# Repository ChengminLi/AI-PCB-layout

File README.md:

# AI PCB Layout

A gift for hardware engineer. 

An AI agent skill for **designing, reviewing, and improving power-electronics PCBs**. This skill does not produce a PCB at the first try, instead it provides a way of how to collobrate with the AI agents to boost the productivity of PCB layout. I expect that the user has at least midlevel hardware experience, thus can provide engineering judgement to review the results.  

The skill teaches an AI coding agent (Cursor, Claude Code, Codex, or any agent that supports `SKILL.md` skills) to work like a careful power-electronics layout engineer: it traces commutation and gate loops from the switching states, derives clearance and copper limits from standards and design currents, and **stops for your approval after every step**, so you stay in control of every design decision.

> **Note:** The skill helps you reach a well-reasoned design and tells you which evidence is still missing. It does not certify safety or EMC compliance. Measurements and the applicable standards remain the final authority.

## What it covers

- **Electrical net table:** worst-case peak voltage, dv/dt, RMS current, and di/dt for each key node and current path, taken from simulation or calculation, and turned into layout constraints
- **Switching loops:** commutation cells, gate charge and discharge loops, Kelvin connections, and common-mode paths, derived per switching transition
- **Insulation:** clearance, creepage, and solid insulation derived from the applicable standard and its inputs, never copied from example values
- **Copper capability:** conductor and via sizing from worst-case RMS current and permitted temperature rise
- **Placement and routing:** functional block floorplans, routability checks, and a routing plan you approve before any copper is drawn
- **Verification:** DRC, insulation geometry, parasitic extraction, re-simulation, and thermal checks, each recorded with its evidence type (CAD check, estimate, simulation, or measurement)
- **Delivery:** fabrication and assembly outputs, and a BOM with verified datasheet and order links

It works with any topology, device technology (Si, IGBT, SiC, GaN), and CAD tool. KiCad 9 is covered in the most detail; concept mappings are included for Altium Designer, Allegro/OrCAD, Xpedition/PADS, and Fusion.

## How it works

The agent works in nine steps. After each step it delivers a short report and waits for you to reply **approve**, **approve with changes**, **redo**, or **stop**.

```mermaid
flowchart TD
    S1["1. Requirements and inputs"] -- gate --> S2["2. Architecture and limits"]
    S2 -- gate --> S3["3. Circuit and models<br/>(end-to-end only)"]
    S3 -- gate --> S4["4. Schematic, footprints, and 3D"]
    S4 -- gate --> S5["5. Design rules and stack-up"]
    S5 -- gate --> S6["6. Placement"]
    S6 -- gate --> S7["7. Routing<br/>(plan first, then block by block)"]
    S7 -- gate --> S8["8. Verification and optimization"]
    S8 -- gate --> S9["9. Delivery"]
```

You don't always need all nine steps. In step 1 you agree on a scope:

| Scope | What happens |
|---|---|
| **Review** an existing design | Reads your files and reports prioritized findings. No files are changed. |
| **Small revision** (label, footprint swap, local reroute) | Proposes the change for approval, then edits and rechecks only what it affects. |
| **Create or revise a layout** for an approved circuit | Footprints, rules, placement, routing, verification, and delivery. |
| **End-to-end design** | All nine steps, from requirements to fabrication files. |

For routing you choose who draws the copper: the agent routes everything, you route and the agent verifies, or a hybrid where the agent routes the critical nets and the rest is autorouted.

## Quick start

### 1. Install the skill

Copy the `power-pcb-design` folder into your agent's skills folder:

| Agent | Skills folder |
|---|---|
| Cursor (all projects) | `~/.cursor/skills/` |
| Cursor (one project) | `<your-project>/.cursor/skills/` |
| Claude Code | `~/.claude/skills/` |
| Codex | `~/.codex/skills/` |

On Windows (PowerShell), for Cursor:

```powershell
git clone https://github.com/ChengminLi/AI-PCB-layout.git
Copy-Item -Recurse AI-PCB-layout\power-pcb-design "$env:USERPROFILE\.cursor\skills\"
```

On macOS or Linux, for Cursor:

```bash
git clone https://github.com/ChengminLi/AI-PCB-layout.git
mkdir -p ~/.cursor/skills && cp -r AI-PCB-layout/power-pcb-design ~/.cursor/skills/
```

No Git? Click **Code → Download ZIP** on this page and copy the `power-pcb-design` folder manually. Restart your agent or open a new chat so it picks up the skill.

### 2. Ask your agent

Open your PCB project folder in the agent and describe what you want. For example:

- *"Review the layout of my 48 V to 12 V synchronous buck in KiCad 9. Don't change any files."*
- *"Improve the gate loop of Q1 and Q2 on my SiC half-bridge board."*
- *"Design a 2-layer 24 V to 5 V, 3 A synchronous buck end to end in KiCad 9."*

The agent will start with step 1: it inspects your files, asks only for the information that changes decisions, and proposes a scope and step plan for your approval.

## Repository layout

```
AI-PCB-layout/
├── power-pcb-design/        The skill
│   ├── SKILL.md             Workflow, review gates, and working rules
│   └── references/          Detailed guidance, read by the agent step by step
├── examples/                Real design examples made with the skill
└── CONTRIBUTING.md          How to add examples or improve the skill
```

The reference files cover the [electrical net table](power-pcb-design/references/electrical-net-table.md), [topologies](power-pcb-design/references/topologies.md), [devices](power-pcb-design/references/devices.md), [regimes and standards](power-pcb-design/references/regimes-and-standards.md), [CAD and tools](power-pcb-design/references/cad-and-tools.md), [electrical layout](power-pcb-design/references/electrical-layout.md), [insulation and copper](power-pcb-design/references/insulation-and-copper.md), [analysis and measurement](power-pcb-design/references/analysis-and-measurement.md), [implementation and delivery](power-pcb-design/references/implementation-and-delivery.md), and [behavioral evaluation](power-pcb-design/references/behavioral-evaluation.md).

## Examples

See [examples/](examples/) for complete boards with their design files, reports, and results.

**[EMC demonstration flyback](examples/emc-flyback-demo/)**: a 24 V to 12 V / 1 A isolated flyback for EMC lectures, with jumper "knobs" that switch filters, gate resistance, snubber, and heatsink potential. KiCad project, LTspice simulations, 39-page design report, and fabrication files.

## Contributing

Design examples, bug reports, and improvements to the skill are welcome. See [CONTRIBUTING.md](CONTRIBUTING.md).

## License

This work is licensed under the [Creative Commons Attribution 4.0 International License (CC BY 4.0)](https://creativecommons.org/licenses/by/4.0/). You may share and adapt it, including for commercial use, as long as you give credit, link to the license, and indicate if you made changes. See [LICENSE](LICENSE) for the full text.

Suggested credit: *"power-pcb-design skill by Chengmin Li, Xiao Yang, https://github.com/ChengminLi/AI-PCB-layout, licensed under CC BY 4.0."*

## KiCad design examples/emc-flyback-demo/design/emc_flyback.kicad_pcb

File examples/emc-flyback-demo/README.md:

# EMC demonstration flyback converter (24 V to 12 V)

A small isolated flyback converter built as a live demonstrator for the EMC lectures at TU/e. Jumpers on the board, the **"EMC knobs"**, switch the filter stages, the switching speed, a snubber, the potential of the heatsink case, the Y-capacitors, and the output earthing, so students can watch the conducted emissions change on two LISNs.

> **Status:** design complete and checked by calculation, simulation, and CAD rule checks. **Not yet prototyped**: the results below are predictions, not measurements.

## Design at a glance

| Item | Value |
|---|---|
| Topology | Isolated flyback, discontinuous conduction mode, peak-current mode control (UC3845B, TL431 and LTV-817S feedback) |
| Input / output | 24 V (20–30 V) in, 12.2 V / 1 A out |
| Switching frequency | 153.6 kHz, just above the 150 kHz start of CISPR band B |
| Devices | IRF520N MOSFET (100 V, TO-220) mounted on the case floor; Würth 750311591 transformer; 2 × SS510C rectifiers in parallel |
| Board | 2 layers, 100 × 76 mm, 1.6 mm FR-4, 1 oz copper |
| Mechanics | Bent 3 mm aluminium U-channel case (112 × 94 × 33 mm) that is also the MOSFET heatsink, with a clear acrylic cover |
| CAD tool | KiCad (version 7 file format; opens in KiCad 7, 8, and 9) |
| Designed with | Claude (AI agent) |
| Scope | End-to-end design, from requirements to fabrication files |
| Revision | E (3 October 2026) |

## The EMC knobs

| Jumper | Setting | Demonstrates |
|---|---|---|
| RG | 4.7 Ω / 22 Ω / 100 Ω gate resistor | Switching speed (5.0 / 2.5 / 0.65 V/ns) versus spectrum |
| CASE | Floating / PGND / chassis / 1 nF | The case is the heatsink: where its common-mode current flows |
| CM1 + CM2 | Common-mode choke bypassed | Effect of the common-mode filter |
| YCAP | Input Y-capacitors to chassis | Y-capacitor return path |
| DM | Differential-mode inductor bypassed | Effect of the differential-mode filter |
| SNUB | 100 pF + 47 Ω drain snubber | Damping of the turn-off ringing |
| YPS | 1 nF / 10 nF primary-to-secondary | External Y-capacitor across the isolation barrier |
| SGCH | Secondary ground to chassis | Earthed output: primary-secondary current through the chassis |

## Images

| | |
|---|---|
|  |  |
| The board in its case. The MOSFET sits under the board with its tab on the case floor. | Top copper. The 3 mm copper-free band in the middle separates primary and secondary. |
|  |  |
| Circuit topology with the jumper knobs in red. | Power-cell loops before (rev D) and after (rev E) the high-frequency re-layout. |

More: [bottom copper](images/pcb-bottom.png), [predicted board temperature](images/thermal-map.png).

## Results and evidence

| Criterion | Result | Evidence type |
|---|---|---|
| Output voltage and ripple | 12.22 V at 1 A, 75 mV peak-to-peak (requirement ≤ 100 mV) | Simulation (ngspice) |
| Loop stability | Phase margin 63–80° over optocoupler CTR 0.5 to 2 | Small-signal model |
| Efficiency | 83.5 % power stage; about 78–79 % for the whole board | Simulation plus loss estimate |
| MOSFET drain peak | 66 V at 24 V in, about 73 V at 30 V in (100 V rating) | Simulation and calculation |
| Loop inductance, rev D → E | Clamp loop 26 → 14 nH, snubber loop 32 → 13 nH, primary power loop 25 → 18 nH | Centre-line estimate (upper bound, for comparison) |
| Clearance and creepage | 0 of 1459 net pairs below IPC-2221B or the design rules; 2.5 mm primary-secondary | Script on the KiCad geometry, plus KiCad DRC |
| DRC and connectivity | 0 clearance errors, 0 unconnected items; schematic and PCB netlists match | CAD check |
| Temperatures at 25 °C | Clamp resistors 70 °C, MOSFET junction 41 °C (58 °C at Rg = 100 Ω) | Board thermal model |
| Conducted emissions | Not yet measured | — |

## Design findings

- **The snubber beats the gate resistor at high frequency.** In simulation, the 100 Ω gate resistor mainly lowers the 5–15 MHz band, while the RC snubber removes the 20–30 MHz ringing peak by about 20 dB. To be confirmed with LISN measurements.
- **The case is the strongest knob.** The MOSFET tab couples about 30 pF into the case. With the case on chassis and no filter, this path alone is estimated at 20–40 dB above the CISPR 32 class B limit; connecting the case to PGND returns the current locally.
- **The RCD clamp is the largest single loss** (0.91 W), more than the MOSFET at the default gate resistor.
- **Rev E shrank the high-frequency loops** by moving the clamp and snubber into the power cell, so they act within about 14 nH of the drain instead of 26–32 nH.
- **Voltage-based design rules in KiCad.** Clearances are set per net class from each net's worst-case voltage (0.6 / 0.4 / 0.2 mm, 2.5 mm across the barrier) in the project's `.kicad_dru` file, so KiCad's DRC and zone filler enforce them.

## Simulation

Two LTspice schematics in [`simulation/`](simulation/), built from the board's component values:

| File | What it simulates |
|---|---|
| `EMC_flyback_power_stage.asc` | Open-loop power stage at a fixed duty cycle: stresses, waveforms, and switching speed versus gate resistor |
| `EMC_flyback_closed_loop.asc` | Power stage plus the real control loop, with behavioural UC3845B, TL431, and LTV-817S models: regulation, load steps, cold start, efficiency |

Keep the files in one folder (clone the repository or use **Code → Download ZIP**): the closed-loop schematic needs `EMC_flyback_control.lib` and the three `.asy` symbols next to it. Each schematic has `.param` knobs (`Rg`, `SNUB`, `CTR`, `Vin`, and others) that match the jumpers on the board. The [simulation README](simulation/README.md) explains how to run them, the suggested experiments, and the reference results.

The schematics were verified in ngspice because LTspice was not available when they were made; if LTspice reports a convergence problem, see the tips at the end of the simulation README. The device models are approximate (behavioural controller models, generic diodes, a fitted MOSFET model), and common-mode paths are not modelled, so use the results for trends and margins.

## Report

The [design report](report/EMC_flyback_design_report.pdf) (39 pages) covers the calculations, simulations, thermal model, layout, mechanics, and the conducted-emission test procedure.

## Files

| Path | Content |
|---|---|
| [`report/`](report/) | Design report (PDF) |
| [`design/`](design/) | KiCad project: open `emc_flyback.kicad_pro`. Includes the custom symbol and footprint libraries, 3D models, and a [schematic PDF](design/emc_flyback_schematic.pdf) |
| [`simulation/`](simulation/) | LTspice schematics (open loop and closed loop), behavioural model library and symbols, plots, and a how-to README |
| [`outputs/`](outputs/) | Gerbers for JLCPCB, JLC BOM and placement files, full BOM with datasheet links, and hand-fitted parts list |
| [`outputs/case/`](outputs/case/) | Workshop drawing of the case and cover (PDF) and their STEP models |
| [`images/`](images/) | 3D renders, copper views, topology, loop and thermal figures |

### Notes

- **Three 3D models are not included** because of manufacturer licensing: the transformer T1 (Würth 750311591), the common-mode choke L1 (Würth 744822222), and the inductor L2 (Bourns SRN8040TA, used for its footprint-compatible body). See [design/EMC_Demo.3dshapes/README.md](design/EMC_Demo.3dshapes/README.md) to add them; without them those parts are simply missing from the 3D view.
- **Case revision.** The case STEP files keep their rev D names. Rev E moved the MOSFET, so check the position of its mounting hole (hole C, 22.74 / 49.68 mm) against the drawing before making a case.
- **Before ordering:** the LCSC number of R9/R10/R20 (UNI-ROYAL 25121WJ0472T4E) is blank in `JLC_BOM.csv`, and L2 (LCSC C37429) may be out of stock; see section 9 of the report.

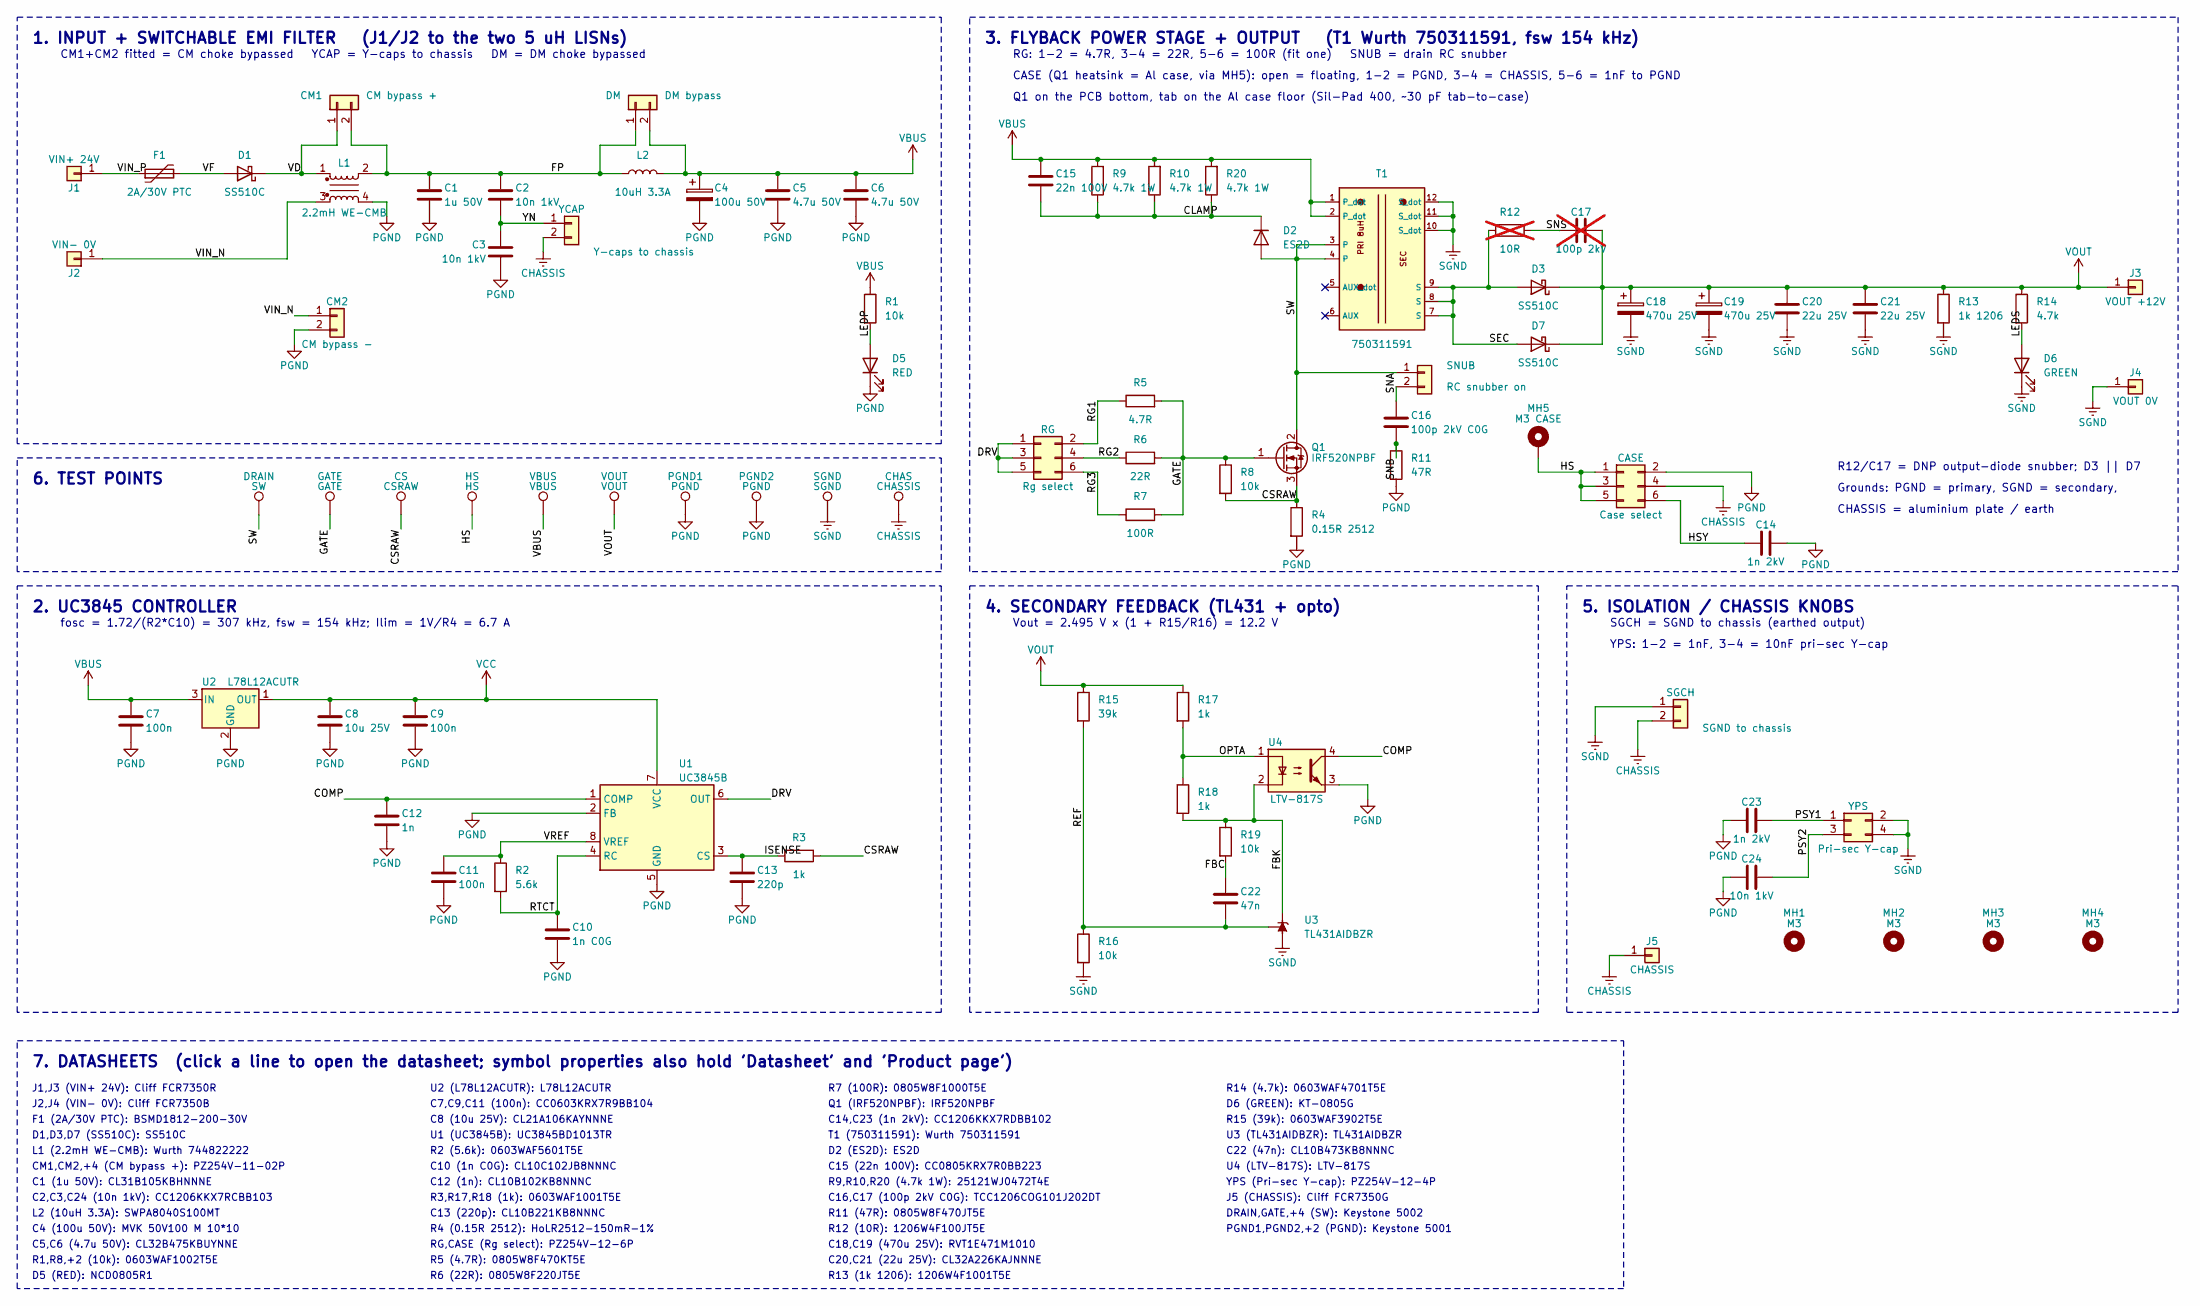
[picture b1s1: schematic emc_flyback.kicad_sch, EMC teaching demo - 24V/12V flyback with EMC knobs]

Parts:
C1: 1u 50V; C_1206_3216Metric; MPN CL31B105KBHNNNE; LCSC C1848
C2, C3, C24: 10n 1kV; C_1206_3216Metric; MPN CC1206KKX7RCBB103; LCSC C107192
C4: 100u 50V; CP_Elec_10x10; MPN MVK 50V100 M 10*10; LCSC C165627
C5, C6: 4.7u 50V; C_1210_3225Metric; MPN CL32B475KBUYNNE; LCSC C170099
C7, C9, C11: 100n; C_0603_1608Metric; MPN CC0603KRX7R9BB104; LCSC C14663
C8: 10u 25V; C_0805_2012Metric; MPN CL21A106KAYNNNE; LCSC C15850
C10: 1n C0G; C_0603_1608Metric; MPN CL10C102JB8NNNC; LCSC C163508
C12: 1n; C_0603_1608Metric; MPN CL10B102KB8NNNC; LCSC C1588
C13: 220p; C_0603_1608Metric; MPN CL10B221KB8NNNC; LCSC C1603
C14, C23: 1n 2kV; C_1206_3216Metric; MPN CC1206KKX7RDBB102; LCSC C23631
C15: 22n 100V; C_0805_2012Metric; MPN CC0805KRX7R0BB223; LCSC C107137
C16: 100p 2kV C0G; C_1206_3216Metric; MPN TCC1206COG101J202DT; LCSC C2833637
C17: 100p 2kV; C_1206_3216Metric; MPN TCC1206COG101J202DT; LCSC C2833637; not fitted
C18, C19: 470u 25V; CP_Elec_10x10; MPN RVT1E471M1010; LCSC C72518
C20, C21: 22u 25V; C_1210_3225Metric; MPN CL32A226KAJNNNE; LCSC C52306
C22: 47n; C_0603_1608Metric; MPN CL10B473KB8NNNC; LCSC C1622
CASE: Case select; PinHeader_2x03_P2.54mm_Vertical; MPN PZ254V-12-6P; LCSC C492420
CHAS: CHASSIS; TestPoint_Keystone_5000-5004_Miniature; MPN Keystone 5001 (black); LCSC C238122
CM1: CM bypass +; PinHeader_1x02_P2.54mm_Vertical; MPN PZ254V-11-02P; LCSC C492401
CM2: CM bypass -; PinHeader_1x02_P2.54mm_Vertical; MPN PZ254V-11-02P; LCSC C492401
CS: CSRAW; TestPoint_Keystone_5000-5004_Miniature; MPN Keystone 5002 (white); LCSC C238123
D1: SS510C; D_SMC; MPN SS510C (reverse-polarity); LCSC C19229
D2: ES2D; D_SMA; MPN ES2D; LCSC C364267
D3, D7: SS510C; D_SMC; MPN SS510C; LCSC C19229
D5: RED; LED_0805_2012Metric; MPN NCD0805R1; LCSC C84256
D6: GREEN; LED_0805_2012Metric; MPN KT-0805G; LCSC C2297
DM: DM bypass; PinHeader_1x02_P2.54mm_Vertical; MPN PZ254V-11-02P; LCSC C492401
DRAIN: SW; TestPoint_Keystone_5000-5004_Miniature; MPN Keystone 5002 (white); LCSC C238123
F1: 2A/30V PTC; Fuse_1812_4532Metric; MPN BSMD1812-200-30V; LCSC C960026
GATE: GATE; TestPoint_Keystone_5000-5004_Miniature; MPN Keystone 5002 (white); LCSC C238123
HS: HS; TestPoint_Keystone_5000-5004_Miniature; MPN Keystone 5002 (white); LCSC C238123
J1: VIN+ 24V; Jack_4mm_RA_Cliff_FCR7350; MPN Cliff FCR7350R (red), 4 mm right-angle 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
J2: VIN- 0V; Jack_4mm_RA_Cliff_FCR7350; MPN Cliff FCR7350B (black), 4 mm right-angl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
J3: VOUT +12V; Jack_4mm_RA_Cliff_FCR7350; MPN Cliff FCR7350R (red), 4 mm right-angle 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
J4: VOUT 0V; Jack_4mm_RA_Cliff_FCR7350; MPN Cliff FCR7350B (black), 4 mm right-angl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
J5: CHASSIS; Jack_4mm_RA_Cliff_FCR7350; MPN Cliff FCR7350G (green), 4 mm right-angl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
L1: 2.2mH WE-CMB; L_CommonMode_Wuerth_WE-CMB-S_744822222; MPN Wurth 744822222 (2.2 mH, 2 A)
L2: 10uH 3.3A; L_Bourns-SRN8040_8x8.15mm; MPN SWPA8040S100MT; LCSC C37429
MH1, MH2, MH3, MH4: M3; MountingHole_3.2mm_M3
MH5: M3 CASE; MountingHole_3.2mm_M3_Pad_Via; MPN M3 x 8 mm metal hex stand-off (female-f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
PGND1, PGND2: PGND; TestPoint_Keystone_5000-5004_Miniature; MPN Keystone 5001 (black); LCSC C238122
Q1: IRF520NPBF; TO-220-3_BottomMount_CaseHeatsink; MPN IRF520NPBF (Infineon); LCSC C2598
R1, R8, R16, R19: 10k; R_0603_1608Metric; MPN 0603WAF1002T5E; LCSC C25804
R2: 5.6k; R_0603_1608Metric; MPN 0603WAF5601T5E; LCSC C23189
R3, R17, R18: 1k; R_0603_1608Metric; MPN 0603WAF1001T5E; LCSC C21190
R4: 0.15R 2512; R_2512_6332Metric; MPN HoLR2512-150mR-1%; LCSC C500726
R5: 4.7R; R_0805_2012Metric; MPN 0805W8F470KT5E; LCSC C17675
R6: 22R; R_0805_2012Metric; MPN 0805W8F220JT5E; LCSC C17561
R7: 100R; R_0805_2012Metric; MPN 0805W8F1000T5E; LCSC C17408
R9, R10, R20: 4.7k 1W; R_2512_6332Metric; MPN 25121WJ0472T4E (UNI-ROYAL)
R11: 47R; R_0805_2012Metric; MPN 0805W8F470JT5E; LCSC C17714
R12: 10R; R_1206_3216Metric; MPN 1206W4F100JT5E; LCSC C17903; not fitted
R13: 1k 1206; R_1206_3216Metric; MPN 1206W4F1001T5E; LCSC C4410
R14: 4.7k; R_0603_1608Metric; MPN 0603WAF4701T5E; LCSC C23162
R15: 39k; R_0603_1608Metric; MPN 0603WAF3902T5E; LCSC C23153
RG: Rg select; PinHeader_2x03_P2.54mm_Vertical; MPN PZ254V-12-6P; LCSC C492420
SGCH: SGND to chassis; PinHeader_1x02_P2.54mm_Vertical; MPN PZ254V-11-02P; LCSC C492401
SGND: SGND; TestPoint_Keystone_5000-5004_Miniature; MPN Keystone 5001 (black); LCSC C238122
SNUB: RC snubber on; PinHeader_1x02_P2.54mm_Vertical; MPN PZ254V-11-02P; LCSC C492401
T1: 750311591; Wurth_750311591_EFD25; MPN Wurth 750311591 (8 uH, 1.5:1:0.67, EFD2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
U1: UC3845B; SOIC-8_3.9x4.9mm_P1.27mm; MPN UC3845BD1013TR; LCSC C7118
U2: L78L12ACUTR; SOT-89-3; MPN L78L12ACUTR; LCSC C69601
U3: TL431AIDBZR; SOT-23; MPN TL431AIDBZR; LCSC C23892
U4: LTV-817S; SMDIP-4_W9.53mm; MPN LTV-817S; LCSC C189217
VBUS: VBUS; TestPoint_Keystone_5000-5004_Miniature; MPN Keystone 5002 (white); LCSC C238123
VOUT: VOUT; TestPoint_Keystone_5000-5004_Miniature; MPN Keystone 5002 (white); LCSC C238123
YCAP: Y-caps to chassis; PinHeader_1x02_P2.54mm_Vertical; MPN PZ254V-11-02P; LCSC C492401
YPS: Pri-sec Y-cap; PinHeader_2x02_P2.54mm_Vertical; MPN PZ254V-12-4P; LCSC C492419

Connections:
AUX_A: T1.5 (AUX_dot)
AUX_B: T1.6 (AUX)
CHASSIS: CASE.4, CHAS.1, J5.1, SGCH.2, YCAP.2
CLAMP: C15.1, D2.1 (K), R9.1, R10.1, R20.1
COMP: C12.1, U1.1 (COMP), U4.4
CSRAW: CS.1, Q1.3 (S), R3.1, R4.1, R8.2
DRV: RG.1, RG.3, RG.5, U1.6 (OUT)
FBC: C22.1, R19.2
FBK: R18.2, R19.1, U3.1 (K), U4.2
FP: C1.1, C2.1, CM1.2, DM.1, L1.2, L2.1
GATE: GATE.1, Q1.1 (G), R5.2, R6.2, R7.2, R8.1
HS: CASE.1, CASE.3, CASE.5, HS.1, MH5.1
HSY: C14.1, CASE.6
ISENSE: C13.1, R3.2, U1.3 (CS)
LEDP: D5.2 (A), R1.2
LEDS: D6.2 (A), R14.2
OPTA: R17.2, R18.1, U4.1
PGND: C1.2, C3.2, C4.2, C5.2, C6.2, C7.2, C8.2, C9.2, C10.2, C11.2, C12.2, C13.2, C14.2, C23.1, C24.1, CASE.2, CM2.2, D5.1 (K), L1.4, PGND1.1, PGND2.1, R4.2, R11.2, U1.2 (FB), U1.5 (GND), U2.2 (GND), U4.3
PSY1: C23.2, YPS.1
PSY2: C24.2, YPS.3
REF: C22.2, R15.2, R16.1, U3.2 (REF)
RG1: R5.1, RG.2
RG2: R6.1, RG.4
RG3: R7.1, RG.6
RTCT: C10.1, R2.2, U1.4 (RC)
SEC: D3.2 (A), D7.2 (A), R12.1, T1.7 (S), T1.8 (S), T1.9 (S)
SGND: C18.2, C19.2, C20.2, C21.2, D6.1 (K), J4.1, R13.2, R16.2, SGCH.1, SGND.1, T1.10 (S_dot), T1.11 (S_dot), T1.12 (S_dot), U3.3 (A), YPS.2, YPS.4
SNA: C16.1, SNUB.2
SNB: C16.2, R11.1
SNS: C17.1, R12.2
SW: D2.2 (A), DRAIN.1, Q1.2 (D), SNUB.1, T1.3, T1.4
VBUS: C4.1, C5.1, C6.1, C7.1, C15.2, DM.2, L2.2, R1.1, R9.2, R10.2, R20.2, T1.1 (P_dot), T1.2 (P_dot), U2.3 (IN), VBUS.1
VCC: C8.1, C9.1, U1.7 (VCC), U2.1 (OUT)
VD: CM1.1, D1.1 (K), L1.1
VF: D1.2 (A), F1.2
VIN_N: CM2.1, J2.1, L1.3
VIN_P: F1.1, J1.1
VOUT: C17.2, C18.1, C19.1, C20.1, C21.1, D3.1 (K), D7.1 (K), J3.1, R13.1, R14.1, R15.1, R17.1, VOUT.1
VREF: C11.1, R2.1, U1.8 (VREF)
YN: C2.2, C3.1, YCAP.1

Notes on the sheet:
1. INPUT + SWITCHABLE EMI FILTER (J1/J2 to the two 5 uH LISNs)
3. FLYBACK POWER STAGE + OUTPUT (T1 Wurth 750311591, fsw 154 kHz)
2. UC3845 CONTROLLER
4. SECONDARY FEEDBACK (TL431 + opto)
5. ISOLATION / CHASSIS KNOBS
6. TEST POINTS
CM1+CM2 fitted = CM choke bypassed YCAP = Y-caps to chassis DM = DM choke bypassed
RG: 1-2 = 4.7R, 3-4 = 22R, 5-6 = 100R (fit one) SNUB = drain RC snubber
CASE (Q1 heatsink = Al case, via MH5): open = floating, 1-2 = PGND, 3-4 = CHASSIS, 5-6 = 1nF to PGND
Q1 on the PCB bottom, tab on the Al case floor (Sil-Pad 400, ~30 pF tab-to-case)
R12/C17 = DNP output-diode snubber; D3 || D7
Grounds: PGND = primary, SGND = secondary,
CHASSIS = aluminium plate / earth
SGCH = SGND to chassis (earthed output)
YPS: 1-2 = 1nF, 3-4 = 10nF pri-sec Y-cap
fosc = 1.72/(R2*C10) = 307 kHz, fsw = 154 kHz; Ilim = 1V/R4 = 6.7 A
Vout = 2.495 V x (1 + R15/R16) = 12.2 V
7. DATASHEETS (click a line to open the datasheet; symbol properties also hold 'Datasheet' and 'Product page')
J1,J3 (VIN+ 24V): Cliff FCR7350R
J2,J4 (VIN- 0V): Cliff FCR7350B
F1 (2A/30V PTC): BSMD1812-200-30V
D1,D3,D7 (SS510C): SS510C
L1 (2.2mH WE-CMB): Wurth 744822222
CM1,CM2,+4 (CM bypass +): PZ254V-11-02P
C1 (1u 50V): CL31B105KBHNNNE
C2,C3,C24 (10n 1kV): CC1206KKX7RCBB103
L2 (10uH 3.3A): SWPA8040S100MT
C4 (100u 50V): MVK 50V100 M 10*10
C5,C6 (4.7u 50V): CL32B475KBUYNNE
R1,R8,+2 (10k): 0603WAF1002T5E
D5 (RED): NCD0805R1
U2 (L78L12ACUTR): L78L12ACUTR
C7,C9,C11 (100n): CC0603KRX7R9BB104
C8 (10u 25V): CL21A106KAYNNNE
U1 (UC3845B): UC3845BD1013TR
R2 (5.6k): 0603WAF5601T5E
C10 (1n C0G): CL10C102JB8NNNC
C12 (1n): CL10B102KB8NNNC
R3,R17,R18 (1k): 0603WAF1001T5E
C13 (220p): CL10B221KB8NNNC

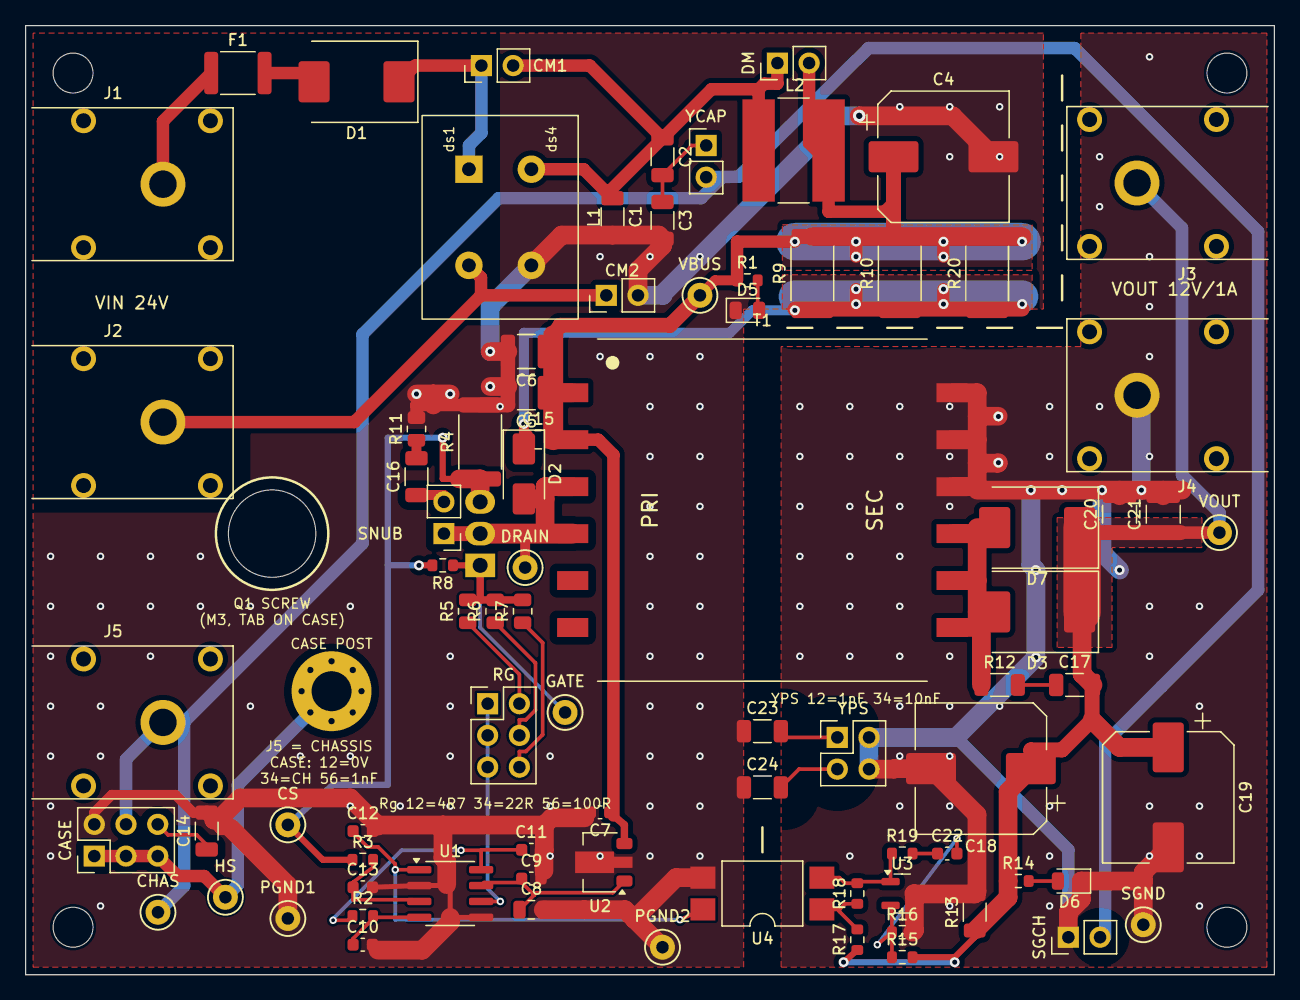
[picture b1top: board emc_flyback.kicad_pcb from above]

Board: 2 copper layers, 100.0 x 76.0 mm, 90 parts (0 on the bottom side), 38 nets.

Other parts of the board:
MECH1: Case_UChannel_revD
MECH2: Cover_PMMA_revD
